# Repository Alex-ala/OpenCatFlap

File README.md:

OpenCatFlap
=====

Work in progress...

Being fed up with SurePets cat flap requiring cloud connection to properly work, I decided to design my own flap.
The 3D model is intended to fit into the SurePet adapter already installed.

I want my flap to have at least these features:
1. Easily managable via an API and/or WebUI/MQTT
2. Powered by battery OR power plug!
3. Easy install via AP/Wifi
4. Motion detection on both sides of the flap to check on where a cat is and where it moves to
5. Light barrier that detects into which direction the flap got opened
6. Light barrier in both sides of the "tunnel" to check into which direction the cat moved
7. Independent control of mechanic in and out control. (My cats outsmart SureFlap by letting each other out/in)
8. Two RFID sensors to detect cats on each side and possibly both!
9. Modular design to easily remove the cover, the electronics and the mechanical parts without having to unscrew screws from the outside.

In addition to that the software should be capable of everything SureFlap is capable of, plus:
1. Set pets as "outdoor only"
2. Quickly and more easily set specific per-cat permissions
3. Manually "unlock once" option for each direction

Current state:
------
**Hardware:**

It is bases on an ESP32 (Arduino Nano ESP32 for development) with various sensors and two servos to lock/unlock.
The 3D model is ready to be tested and a printed version is already in use to debug the code. Slight adjustments to the
antenna design will be done in future.

Used vital parts:
- 2x PIR (motion detection): Panasonic AMN33111, testing with cheaper options
- 2x light barrier for flap detection: TCST 1103
- 2x light barrier for tunnel passage: IR LED + NE555 and TSOP18*38 and TSOP18*56
- 2x RFID reader: EM4095
- 2x Servo: DSM44

**Software:**

The software runs a main process that handles global configs and aggregates events reported by the two state machines.
After the last hardware overhaul, quite some work is to be done to update sensors and reading RFID from EM4095 instead of WL-134

## State machines
The locking and unlocking logic is split up into two independent state machines, one for each direction of travel.
One state machine handles the PIR, RFID and Servo on one side of the cat flap.

This way the flap can idependently unlock for ougoing or incoing cats without acidentally opening the other direction aswell, allowing false passages.

Roughly speaking there are 3 states: Idle (only PIR active to wait for motion), Reading (RFID enabled when motion is detected) and unlocked (when a correct RFID is read).

## Wifi

If no Wifi is configured, the flap acts as an AP opening an open "OpenCatFlap" wifi. One can either use this wifi for full control via api, or send credentials to connect to an existing wifi.

## MQTT

MQTT can be configured to connect to an existing MQTT server. The flap will then send events to topics `opencatflap/<flapname>/<type>`.
Configuration via MQTT is planned.

## Webserver

Current means to configure the flap is via http. There is a webserver running on :80 that takes requests to configure wifi, mqtt, lock allowance and cats, aswell as getting some status information.

How to configure (for now):
Wifi: `curl -H "Content-Type: application/json" http://192.168.4.1/api -d '{"command": "wifiConfig", "ssid": "Bockenburg", "passphrase": "", "ntpServer": "ip preffered, hostname possible"}'`
MQTT: `curl -H "Content-Type: application/json" 'http://10.5.0.60/api' -d'{"command": "mqttConfig", "server": "mosquitto.ahome", "port": 8011, "ssl": true, "logActivity": true}'`
MQTT Certificates: 
```
curl -H "Content-Type: text/plain" 'http://10.5.0.60/api/certs?name=key' --data-binary @/home/alex/trash/opencatflap.key
curl -H "Content-Type: text/plain" 'http://10.5.0.60/api/certs?name=cert' --data-binary @/home/alex/trash/opencatflap.crt
curl -H "Content-Type: text/plain" 'http://10.5.0.60/api/certs?name=ca' --data-binary @/home/alex/trash/ca.crt
```

## Getting started with a new Arduino Nano ESP32

A new board ships with Arduino's stock partition table, which has no `spiffs` partition. DFU uploads only replace the app, so the first flash has to be done with esptool. Otherwise the webserver fails with `File system is not mounted`.

1. In `platformio.ini`, make sure `upload_protocol = esptool` is active in `[env:arduino_nano_esp32]`.
2. Optional: put `wifi_configuration.json`, `mqtt_configuration.json` and the MQTT certificates into `data/` to have them preinstalled. They are ignored by git and can also be set later via the API.
3. Close any serial monitor and enter bootloader mode: connect B1 to GND, press reset, then remove the connection. The board now shows up as `303a:1001` in `lsusb`.
4. Flash the bootloader, partition table and firmware:
   ```
   pio run -e arduino_nano_esp32 -t upload
   ```
5. Flash the filesystem. If the board left bootloader mode, repeat step 3 first. This replaces everything on the filesystem with the contents of `data/`.
   ```
   pio run -e arduino_nano_esp32 -t uploadfs
   ```
6. Press reset and wait about 20 seconds for the flap to boot.
7. Without a Wifi config, connect to the open "OpenCatFlap" wifi and open http://192.168.4.1. Configure Wifi and MQTT as described above.

The partition table only has to be flashed once per board. Afterwards, firmware updates can use DFU (comment out `upload_protocol = esptool`) or the `arduino_nano_esp32_ota` environment. Filesystem uploads always need esptool.

**Future Improvements:**
- NE555 is too inconsistant due to 5% tolerance capacitor with bad temperature coefficient
- Tuning condensators for EM4095 have to be bigger to allow more jiggle-room when building an antenna
- Condensators to configure EM4095 need to have better tolerance and temperature coefficient to get as close to required frequency as possible. Current ones allow reading big chips, small tubes and implanted ones need a lot of hugging the antenna.
- Cheaper connectors for the PCB and external sensors
- Battery backup circuit
- ESP32 directly onboard

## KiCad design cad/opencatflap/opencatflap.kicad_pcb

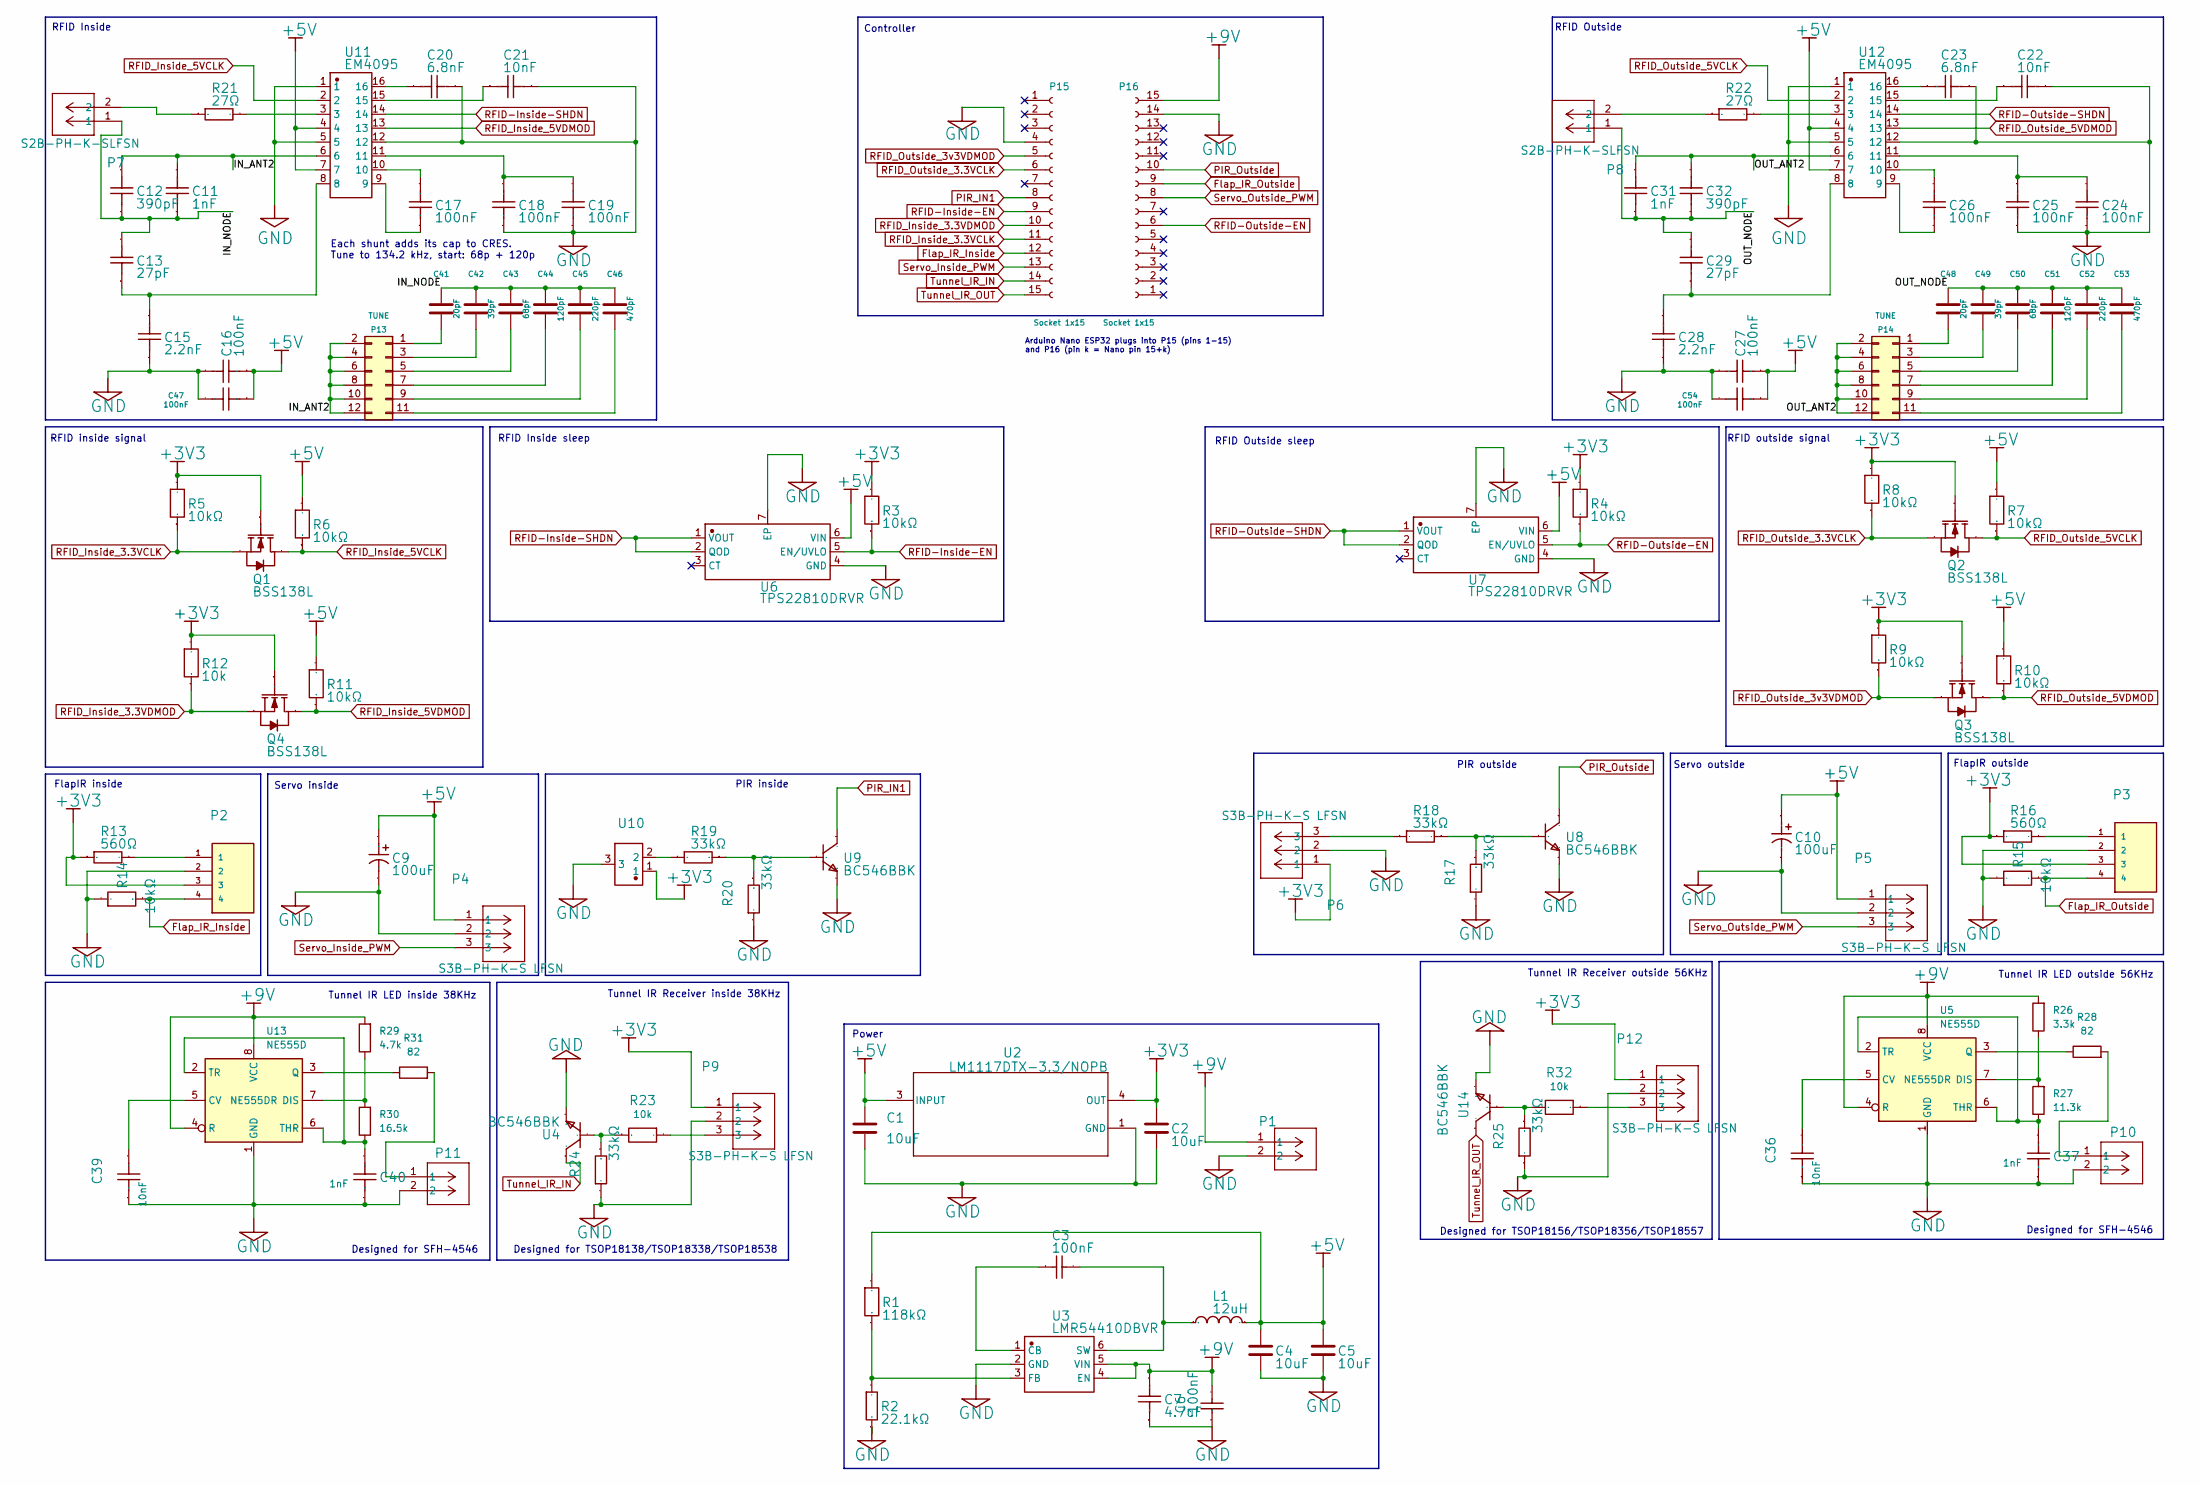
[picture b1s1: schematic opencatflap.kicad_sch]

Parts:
C1, C2, C4, C5: 10uF; CAP_CL31A_SAM; Manufacturer Part CL31A106KBHNNNE; LCSC C13585
C3, C6: 100nF; C_1210_3225Metric; Manufacturer Part CC1210KKX7R0BB104; LCSC C527375
C7: 4.7uF; C_1206_3216Metric; Manufacturer Part CC1206KKX7R9BB475; LCSC C132170
C9, C10: 100uF; CP_Elec_6.3x7.7; Manufacturer Part VH1E101ME077000CE0; LCSC C240513
C11, C31: 1nF; C_1206_3216Metric; Manufacturer Part CC1206JKNPOCBN102; LCSC C113872
C12, C32: 390pF; C_1206_3216Metric; Manufacturer Part CC1206JKNPOCBN391; LCSC C326659
C13, C29: 27pF; C_1206_3216Metric; Manufacturer Part CC1206JKNPOCBN270; LCSC C541492
C15, C28: 2.2nF; C_0603_1608Metric; Manufacturer Part CC0603FRNPO9BN222; LCSC C576780
C16, C17, C18, C19, C24, C25, C26, C27, C47, C54: 100nF; C_0603_1608Metric; Manufacturer Part CC0603KRX7R9BB104; LCSC C14663
C20, C23: 6.8nF; C_0603_1608Metric; Manufacturer Part 0603B682K500NT; LCSC C1631
C21, C22, C36, C39: 10nF; C_0603_1608Metric; Manufacturer Part 0603B103K500NT; LCSC C57112
C37, C40: 1nF; C_0603_1608Metric; Manufacturer Part CC0603FRNPO9BN102; LCSC C309468
C41, C48: 20pF; C_1206_3216Metric; Manufacturer Part CC1206JKNPOCBN200; LCSC C577124
C42, C49: 39pF; C_1206_3216Metric; Manufacturer Part CC1206JKNPOCBN390; LCSC C541493
C43, C50: 68pF; C_1206_3216Metric; Manufacturer Part CC1206JKNPOCBN680; LCSC C107178
C44, C51: 120pF; C_1206_3216Metric; Manufacturer Part CC1206JKNPOCBN121; LCSC C113873
C45, C52: 220pF; C_1206_3216Metric; Manufacturer Part CC1206JKNPOCBN221; LCSC C107175
C46, C53: 470pF; C_1206_3216Metric; Manufacturer Part CC1206JKNPOCBN471; LCSC C107177
L1: 12uH; L_Changjiang_FNR6045S; Manufacturer Part FNR6045S120MT; LCSC C168077
P1, P7, P8, P11: S2B-PH-K-SLFSN; CONN_S2B-PH-K-S_JST; Manufacturer Part S2B-PH-K-S(LF)(SN); LCSC C173752
P2, P3: S4B-PH-K-S_LF__SN_; CONN_S4B-PH-K-S_JST; Manufacturer Part S4B-PH-K-S(LF)(SN); LCSC C157926
P4, P5, P6, P9, P12: S3B-PH-K-S LFSN; CONN_S3B-PH-K-S_JST; Manufacturer Part S3B-PH-K-S(LF)(SN); LCSC C157929
P10: IL-G-2P-S3T2-SA; CONN_S2B-PH-K-S_JST; Manufacturer Part S2B-PH-K-S(LF)(SN); LCSC C173752
P13, P14: TUNE; PinHeader_2x06_P2.54mm_Vertical; Manufacturer Part HX PZ2.54-2x6P ZZ; LCSC C32713279
P15, P16: Socket 1x15; PinSocket_1x15_P2.54mm_Vertical; Manufacturer Part HX PM2.54-1x15P ZC; LCSC C41417327
Q1, Q2, Q3, Q4: BSS138L; Manufacturer Part BSS138L; LCSC C890265
R1: 118kΩ; R_0603_1608Metric; Manufacturer Part RT0603FRE07118KL; LCSC C863548
R2: 22.1kΩ; R_0603_1608Metric; Manufacturer Part RC0603FR-0722K1L; LCSC C137768
R3, R4, R5, R6, R7, R8, R9, R10, R11, R14, R15: 10kΩ; R_0603_1608Metric; Manufacturer Part 0603WAF1002T5E; LCSC C25804
R12, R23, R32: 10k; R_0603_1608Metric; Manufacturer Part 0603WAF1002T5E; LCSC C25804
R13, R16: 560Ω; R_0603_1608Metric; Manufacturer Part 0603WAF5600T5E; LCSC C23204
R17, R18, R19, R20, R24, R25: 33kΩ; R_0603_1608Metric; Manufacturer Part 0603WAF3302T5E; LCSC C4216
R21, R22: 27Ω; R_2512_6332Metric; Manufacturer Part RC2512FK-0727RL; LCSC C877905
R26: 3.3k; R_0603_1608Metric; Manufacturer Part 0603WAF3301T5E; LCSC C22978
R27: 11.3k; R_0603_1608Metric; Manufacturer Part 0603WAF1132T5E; LCSC C22860
R28, R31: 82; R_0603_1608Metric; Manufacturer Part RC0603FR-0782RL; LCSC C137676
R29: 4.7k; R_0603_1608Metric; Manufacturer Part 0603WAF4701T5E; LCSC C23162
R30: 16.5k; R_0603_1608Metric; Manufacturer Part 0603WAF1652T5E; LCSC C22812
U2: LM1117DTX-3.3/NOPB; LM1117DTX-3.3NOPB; Manufacturer Part LM1117DTX-3.3/NOPB; LCSC C73181
U3: LMR54410DBVR; U_SOT-23_TEX; Manufacturer Part LMR54410DBVR; LCSC C3200265
U4, U8, U9, U14: BC546BBK; TO-92L_Inline; Manufacturer Part BC546BBK; LCSC C3201532
U5, U13: NE555D; SOIC-8_3.9x4.9mm_P1.27mm; Manufacturer Part NE555DR; LCSC C7593
U6, U7: TPS22810DRVR; DRV0006A_NV; Manufacturer Part TPS22810DRVR; LCSC C527679
U10: SB312; PinHeader_1x03_P2.54mm_Vertical; Manufacturer Part SB312; LCSC C96133
U11, U12: EM4095; Manufacturer Part EM4095HMSO16B+; LCSC C17203964

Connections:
+3V3: C2.1, P2.3, P3.3, P6.1, P9.1, P12.1, Q1.1 (G), Q2.1 (G), Q3.1 (G), Q4.1 (G), R3.2, R4.2, R5.2, R8.2, R9.2, R12.2, R13.1, R16.1, U2.4 (OUT), U10.1
+5V: C1.1, C4.1, C5.1, C9.1, C10.1, C16.1, C27.1, C47.1, C54.1, L1.2, P4.1, P5.1, R1.2, R6.2, R7.2, R10.2, R11.2, U2.3 (INPUT), U6.6 (VIN), U7.6 (VIN), U11.4, U11.7, U12.4, U12.7
+9V: C6.2, C7.2, P1.1, P16.15, R26.2, R29.2, U3.4 (EN), U3.5 (VIN), U5.4 (R), U5.8 (VCC), U13.4 (R), U13.8 (VCC)
/IN_ANT2: C11.2, C12.2, P13.2, P13.4, P13.6, P13.8, P13.10, P13.12, U11.6
/IN_NODE: C11.1, C12.1, C13.2, C41.1, C42.1, C43.1, C44.1, C45.1, C46.1, P7.1
/OUT_ANT2: C31.2, C32.2, P14.2, P14.4, P14.6, P14.8, P14.10, P14.12, U12.6
/OUT_NODE: C29.2, C31.1, C32.1, C48.1, C49.1, C50.1, C51.1, C52.1, C53.1, P8.1
Flap_IR_Inside: P2.4, P15.12, R14.1
Flap_IR_Outside: P3.4, P16.9, R15.1
GND: C1.2, C2.2, C4.2, C5.2, C6.1, C7.1, C9.2, C10.2, C15.1, C16.2, C18.1, C19.1, C20.2, C21.2, C22.2, C23.2, C24.1, C25.1, C27.2, C28.1, C36.1, C37.1, C39.1, C40.1, C47.2, C54.2, P1.2, P2.2, P3.2, P4.2, P5.2, P6.2, P9.2, P10.2, P11.2, P12.2, P15.4, P16.14, R2.1, R14.2, R15.2, R17.2, R20.2, R24.2, R25.2, U2.1 (GND), U3.2 (GND), U4.3 (E), U5.1 (GND), U6.4 (GND), U6.7 (EP), U7.4 (GND), U7.7 (EP), U8.3 (E), U9.3 (E), U10.3, U11.1, U11.5, U11.12, U12.1, U12.5, U12.12, U13.1 (GND), U14.3 (E); also elsewhere on the board
unnamed: C13.1, C15.2, U11.8
unnamed: C17.1, U11.9
unnamed: C17.2, U11.10
unnamed: C18.2, C19.2, U11.11
unnamed: C20.1, U11.16
unnamed: C21.1, U11.15
unnamed: C22.1, U12.15
unnamed: C23.1, U12.16
unnamed: C24.2, C25.2, U12.11
unnamed: C26.1, U12.9
unnamed: C26.2, U12.10
unnamed: C28.2, C29.1, U12.8
unnamed: P2.1, R13.2
unnamed: P3.1, R16.2
unnamed: P6.3, R18.2
unnamed: P7.2, R21.1
unnamed: P8.2, R22.1
unnamed: P9.3, R23.2
unnamed: P10.1, R28.2
unnamed: P11.1, R31.2
unnamed: P12.3, R32.2
unnamed: C41.2, P13.1
unnamed: C42.2, P13.3
unnamed: C43.2, P13.5
unnamed: C44.2, P13.7
unnamed: C45.2, P13.9
unnamed: C46.2, P13.11
unnamed: C48.2, P14.1
unnamed: C49.2, P14.3
unnamed: C50.2, P14.5
unnamed: C51.2, P14.7
unnamed: C52.2, P14.9
unnamed: C53.2, P14.11
unnamed: R19.2, U10.2
unnamed: R21.2, U11.3
unnamed: R22.2, U12.3
unnamed: C3.1, U3.1 (CB)
unnamed: R1.1, R2.2, U3.3 (FB)
unnamed: C3.2, L1.1, U3.6 (SW)
unnamed: R23.1, R24.1, U4.2 (B)
unnamed: C36.2, U5.5 (CV)
unnamed: R26.1, R27.2, U5.7 (DIS)
unnamed: R28.1, U5.3 (Q)
unnamed: C37.2, R27.1, U5.2 (TR), U5.6 (THR)
unnamed: R17.1, R18.1, U8.2 (B)
unnamed: R19.1, R20.1, U9.2 (B)
unnamed: C39.2, U13.5 (CV)
unnamed: R29.1, R30.2, U13.7 (DIS)
unnamed: R31.1, U13.3 (Q)
unnamed: C40.2, R30.1, U13.2 (TR), U13.6 (THR)
unnamed: R25.1, R32.1, U14.2 (B)
PIR_IN1: P15.8, U9.1 (C)
PIR_Outside: P16.10, U8.1 (C)
RFID-Inside-EN: P15.9, R3.1, U6.5 (EN/UVLO)
RFID-Inside-SHDN: U6.1 (VOUT), U6.2 (QOD), U11.14
RFID-Outside-EN: P16.6, R4.1, U7.5 (EN/UVLO)
RFID-Outside-SHDN: U7.1 (VOUT), U7.2 (QOD), U12.14
RFID_Inside_3.3VCLK: P15.11, Q1.2 (S), R5.1
RFID_Inside_3.3VDMOD: P15.10, Q4.2 (S), R12.1
RFID_Inside_5VCLK: Q1.3 (D), R6.1, U11.2
RFID_Inside_5VDMOD: Q4.3 (D), R11.1, U11.13
RFID_Outside_3.3VCLK: P15.6, Q2.2 (S), R8.1
RFID_Outside_3v3VDMOD: P15.5, Q3.2 (S), R9.1
RFID_Outside_5VCLK: Q2.3 (D), R7.1, U12.2
RFID_Outside_5VDMOD: Q3.3 (D), R10.1, U12.13
Servo_Inside_PWM: P4.3, P15.13
Servo_Outside_PWM: P5.3, P16.8
Tunnel_IR_IN: P15.14, U4.1 (C)
Tunnel_IR_OUT: P15.15, U14.1 (C)

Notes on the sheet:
FlapIR inside
Tunnel IR Receiver outside 56KHz
FlapIR outside
Designed for TSOP18138/TSOP18338/TSOP18538
Controller
PIR outside
Tunnel IR LED inside 38KHz
Servo outside
Designed for SFH-4546
Arduino Nano ESP32 plugs into P15 (pins 1-15) and P16 (pin k = Nano pin 15+k)
Designed for TSOP18156/TSOP18356/TSOP18557
RFID Outside
RFID inside signal
RFID Outside sleep
Power
Servo inside
RFID outside signal
PIR inside
RFID Inside
RFID Inside sleep
Tunnel IR LED outside 56KHz
Tunnel IR Receiver inside 38KHz
Each shunt adds its cap to CRES. Tune to 134.2 kHz, start: 68p + 120p

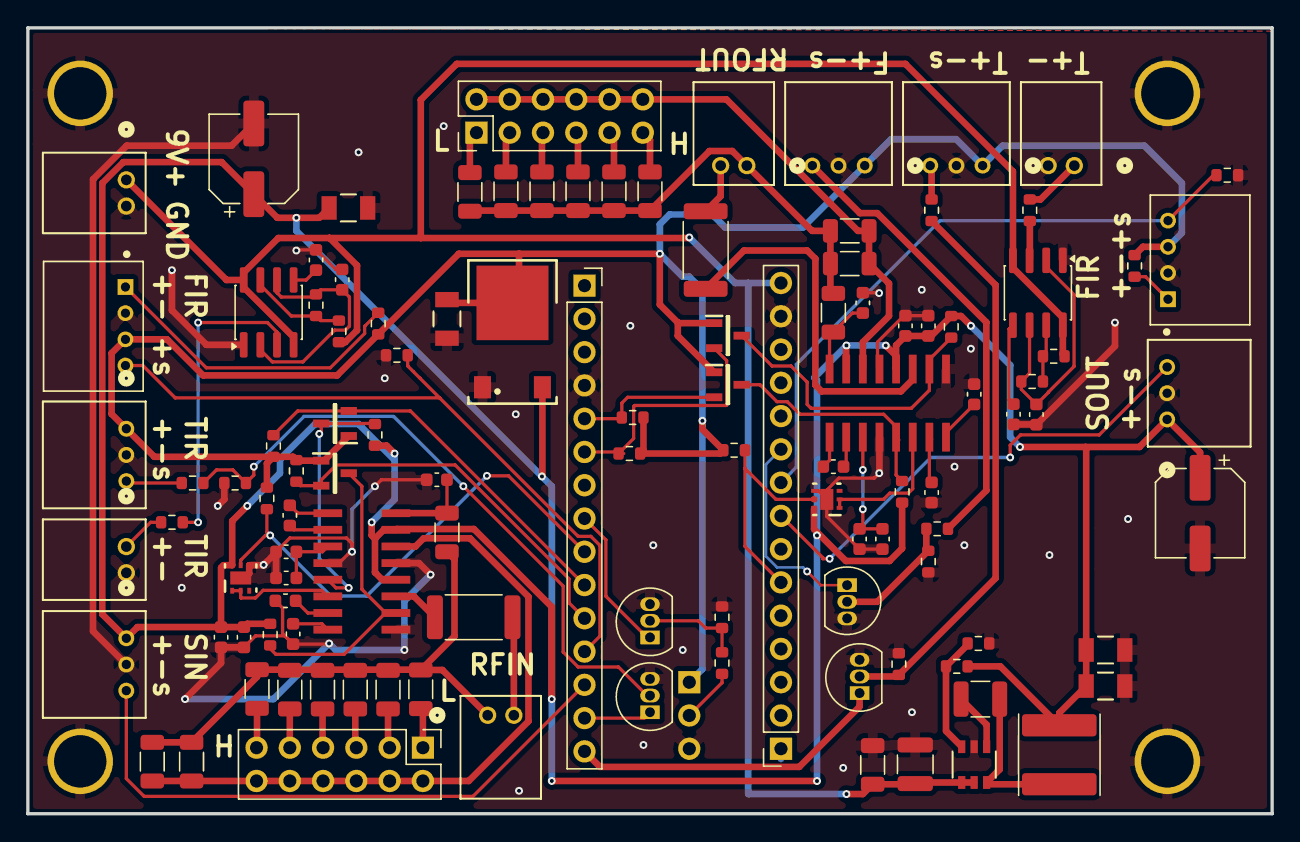
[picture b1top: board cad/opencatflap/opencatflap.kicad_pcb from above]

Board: 2 copper layers, 95.0 x 60.0 mm, 117 parts (1 on the bottom side), 79 nets.

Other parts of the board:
Pad_gge19202, Pad_gge19226, Pad_gge19274, Pad_gge19274#2: Bohrloch

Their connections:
GND: Pad_gge19202.1, Pad_gge19226.1, Pad_gge19274.1, Pad_gge19274#2.1; also elsewhere on the board

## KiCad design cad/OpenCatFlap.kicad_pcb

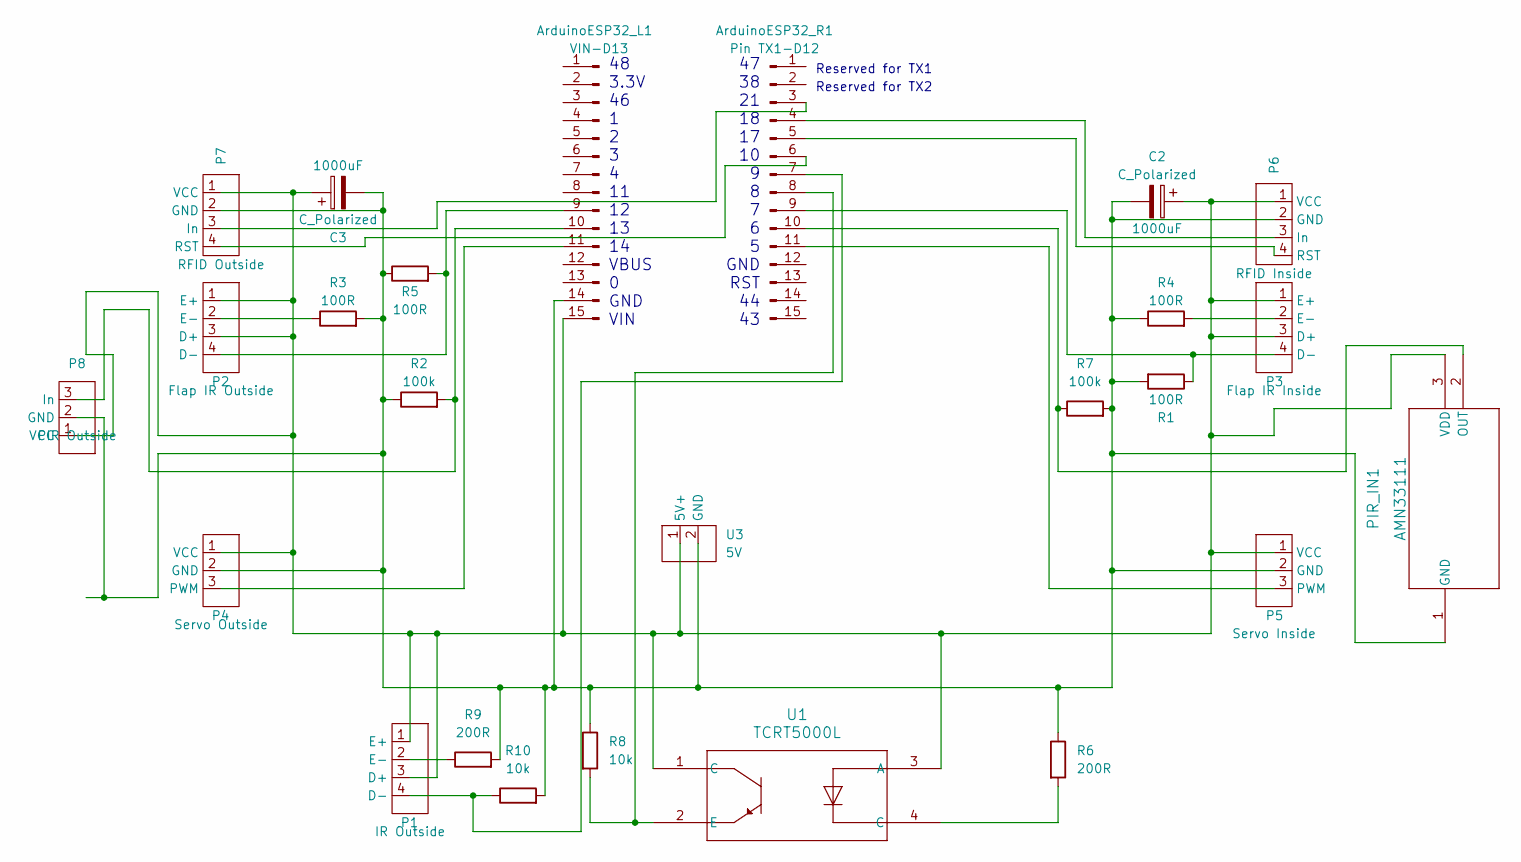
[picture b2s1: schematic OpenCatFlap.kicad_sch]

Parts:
ArduinoESP32_L1: VIN-D13; PinHeader_1x15_P2.54mm_Vertical
ArduinoESP32_R1: Pin TX1-D12; PinHeader_1x15_P2.54mm_Vertical
C2, C3: C_Polarized; CP_Elec_8x10
P1: IR Outside; PinHeader_1x04_P2.54mm_Vertical
P2: Flap IR Outside; PinHeader_1x04_P2.54mm_Vertical
P3: Flap IR Inside; PinHeader_1x04_P2.54mm_Vertical
P4: Servo Outside; PinHeader_1x03_P2.54mm_Vertical
P5: Servo Inside; PinHeader_1x03_P2.54mm_Vertical
P6: RFID Inside; PinHeader_1x04_P2.54mm_Vertical
P7: RFID Outside; PinHeader_1x04_P2.54mm_Vertical
P8: PIR Outside; PinHeader_1x03_P2.54mm_Vertical
PIR_IN1: AMN33111; AMN33111_PAN
R1, R3, R4, R5: 100R; R_0805_2012Metric
R2, R7: 100k; R_0805_2012Metric
R6, R9: 200R; R_0805_2012Metric
R8, R10: 10k; R_0805_2012Metric
U1: TCRT5000L; TCRT5000_VIS
U3: 5V; PinHeader_1x02_P2.54mm_Vertical

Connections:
unnamed: ArduinoESP32_L1.9, P2.4 (D-), R5.2
unnamed: ArduinoESP32_L1.10, P8.3 (In), R2.2
unnamed: ArduinoESP32_L1.11, P4.3 (PWM)
unnamed: ArduinoESP32_L1.14, C2.2, C3.2, P4.2 (GND), P5.2 (GND), P6.2 (GND), P7.2 (GND), P8.2 (GND), PIR_IN1.1 (GND), R1.2, R2.1, R3.2, R4.1, R5.1, R6.1, R7.2, R8.1, R9.2, R10.2, U3.2 (GND)
unnamed: ArduinoESP32_L1.15, C2.1, C3.1, P1.1 (E+), P1.3 (D+), P2.1 (E+), P2.3 (D+), P3.1 (E+), P3.3 (D+), P4.1 (VCC), P5.1 (VCC), P6.1 (VCC), P7.1 (VCC), P8.1 (VCC), PIR_IN1.3 (VDD), U1.1 (C), U1.3 (A), U3.1 (5V+)
unnamed: ArduinoESP32_R1.3, P7.3 (In)
unnamed: ArduinoESP32_R1.4, P6.3 (In)
unnamed: ArduinoESP32_R1.5, P6.4 (RST)
unnamed: ArduinoESP32_R1.6, P7.4 (RST)
unnamed: ArduinoESP32_R1.7, P1.4 (D-), R10.1
unnamed: ArduinoESP32_R1.8, R8.2, U1.2 (E)
unnamed: ArduinoESP32_R1.9, P3.4 (D-), R1.1
unnamed: ArduinoESP32_R1.10, PIR_IN1.2 (OUT), R7.1
unnamed: ArduinoESP32_R1.11, P5.3 (PWM)
unnamed: P1.2 (E-), R9.1
unnamed: P2.2 (E-), R3.1
unnamed: P3.2 (E-), R4.2
unnamed: R6.2, U1.4 (C)

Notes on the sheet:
Reserved for TX2
48 3.3V 46 1 2 3 4 11 12 13 14 VBUS 0 GND VIN
47 38 21 18 17 10 9 8 7 6 5 GND RST 44 43
Reserved for TX1

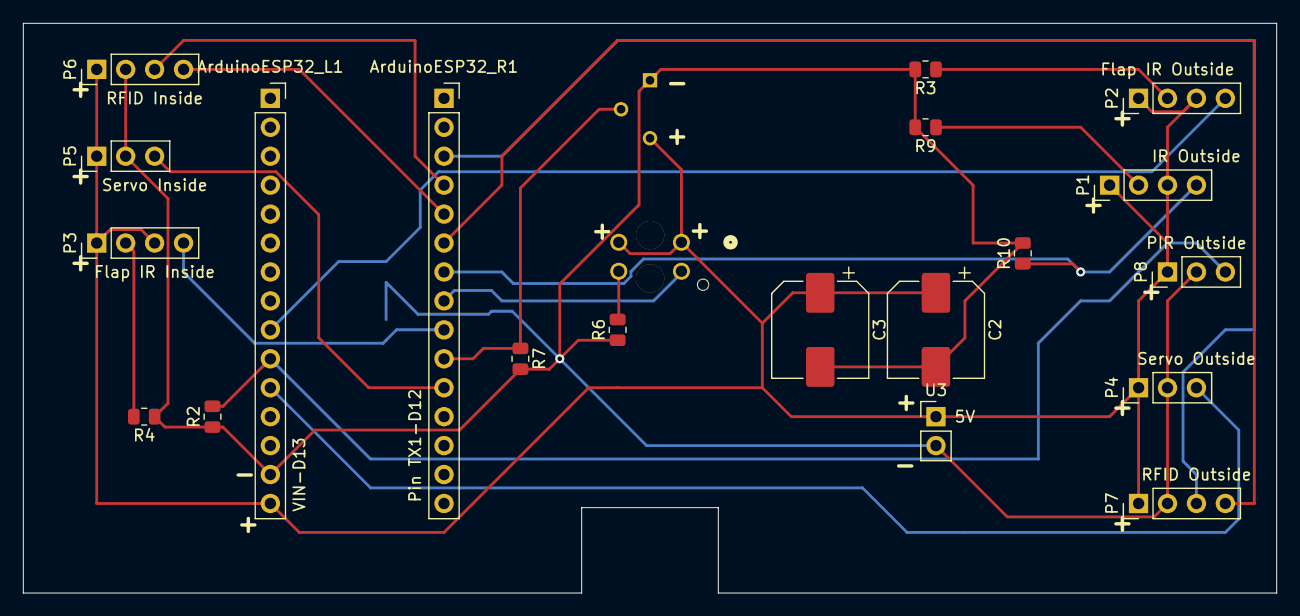
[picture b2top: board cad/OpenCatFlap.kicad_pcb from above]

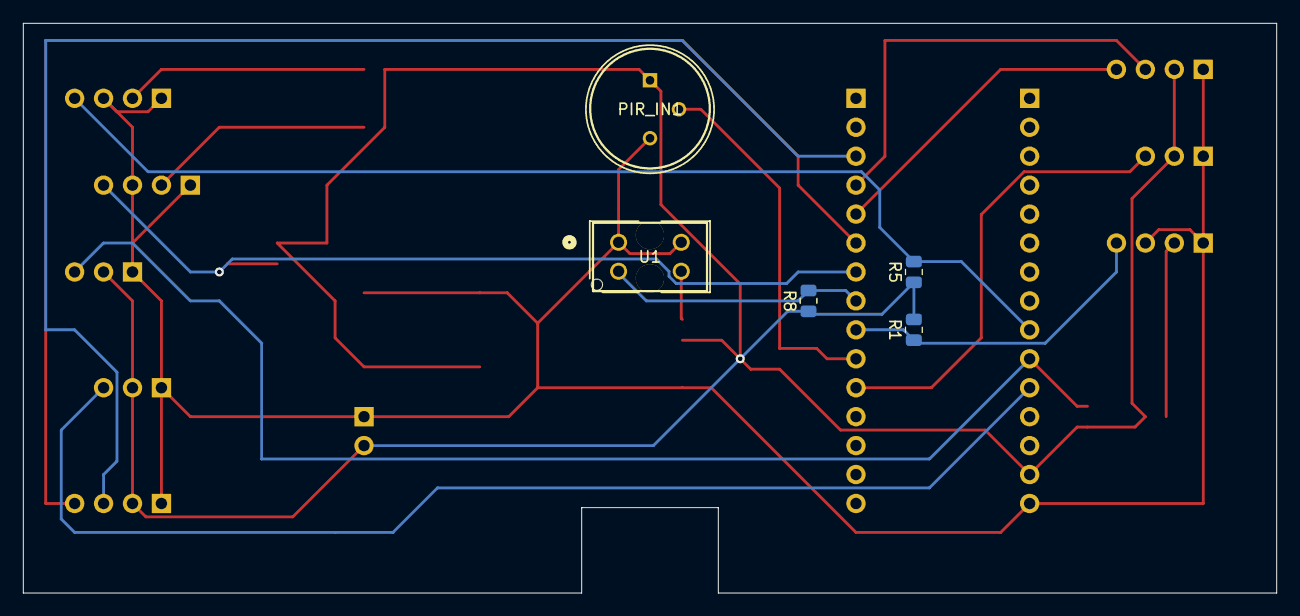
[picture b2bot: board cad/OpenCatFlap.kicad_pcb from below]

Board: 2 copper layers, 110.0 x 50.0 mm, 25 parts (5 on the bottom side), 18 nets.

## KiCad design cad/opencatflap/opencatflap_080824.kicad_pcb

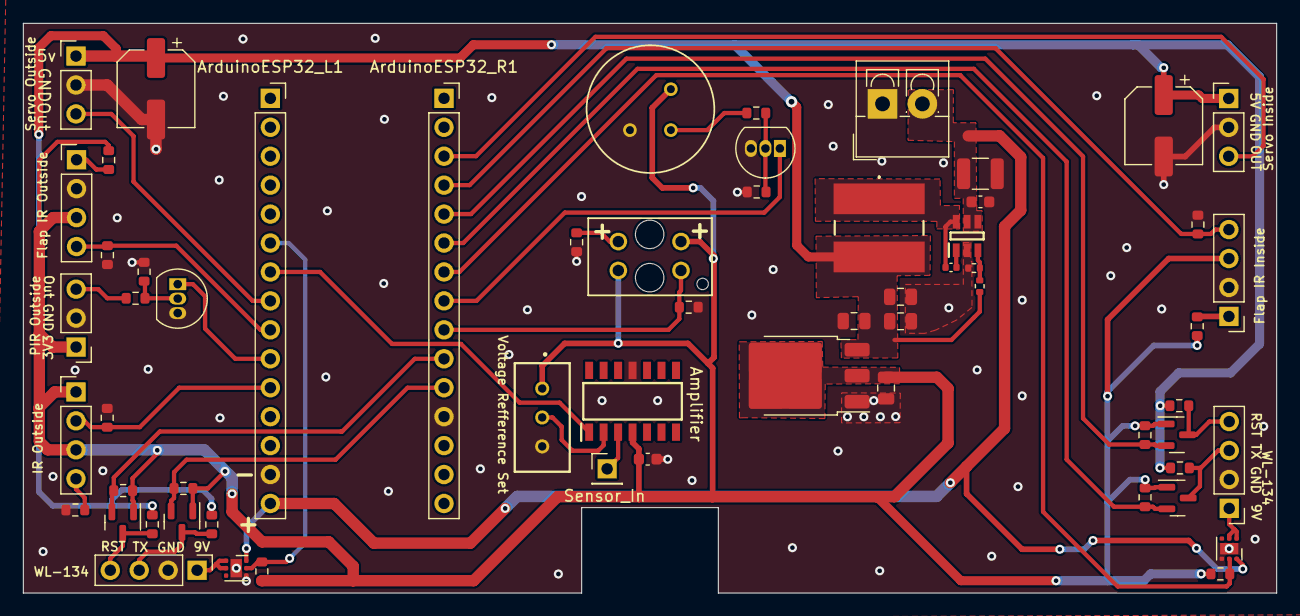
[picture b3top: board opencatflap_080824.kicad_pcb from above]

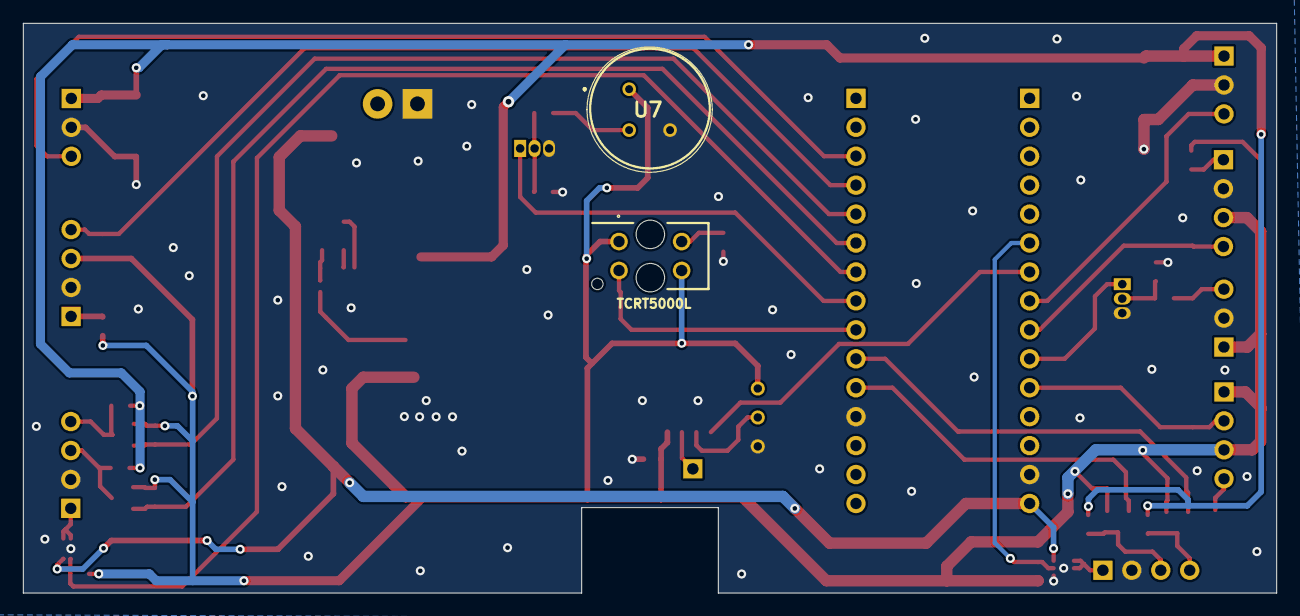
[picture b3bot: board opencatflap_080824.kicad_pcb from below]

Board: 2 copper layers, 110.0 x 50.0 mm, 61 parts (2 on the bottom side), 38 nets.

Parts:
ArduinoESP32_L1: VIN-D13; PinSocket_1x15_P2.54mm_Vertical
ArduinoESP32_R1: Pin TX1-D12; PinSocket_1x15_P2.54mm_Vertical
C1, C2, C5, C7: 10u; C_0805_2012Metric
C3: 100n; C_0402_1005Metric
C4: 4.7u; C_1210_3225Metric
C6, C10: 100n; C_0603_1608Metric
C8, C9: 100u; CP_Elec_6.3x7.7
J1: Screw_Terminal_01x02; TerminalBlock_4Ucon_1x02_P3.50mm_Vertical
J2: Screw_Terminal_01x04; PinHeader_1x04_P2.54mm_Vertical
J3: Screw_Terminal_01x01; PinHeader_1x01_P2.54mm_Vertical
L1: 12u; SDR0805120ML
P1: PIR Outside; PinHeader_1x03_P2.54mm_Vertical
P2: Flap IR Inside; PinHeader_1x04_P2.54mm_Vertical
P4: Flap IR Outside; PinHeader_1x04_P2.54mm_Vertical
P9: RFID Inside; PinHeader_1x04_P2.54mm_Vertical
P10: RFID OutSide; PinHeader_1x04_P2.54mm_Vertical
P11: Servo Inside; PinHeader_1x03_P2.54mm_Vertical
P12: Servo Outside; PinHeader_1x03_P2.54mm_Vertical
Q1, Q2, Q3, Q4: BSS138; SOT-23
Q5, Q6: BC546B; TO-92_Inline
R1, R26: 200R; R_0603_1608Metric
R2, R7, R8, R9: 33k; R_0603_1608Metric
R3, R4, R6, R11, R12, R13, R14, R15, R16, R18, R20, R22, R24, R25: 10k; R_0603_1608Metric
R5, R21: 566R; R_0603_1608Metric
R10: 118k; R_0402_1005Metric
R23: 22.1k; R_0402_1005Metric
RV1: 10k; 3296W-1
U1, U2: TPS22810DRV; WSON-6-1EP_2x2mm_P0.65mm_EP1x1.6mm
U3: LM1117DT-3.3; TO-252-3_TabPin2
U4: LM324; SOIC127P600X175-14N
U5: TCRT5000L
U6: LMR54410DBVR
U7: AMN33111

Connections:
+3V3: C2.1, C10.1, J2.1, J2.3, P1.1 (VCC), P2.3 (D+), P4.3 (D+), Q1.1 (G), Q2.1 (G), Q3.1 (G), Q4.1 (G), R4.1, R5.2, R11.1, R13.1, R15.1, R16.1, R20.1, R21.2, RV1.1, U3.2 (VO), U4.4 (V+), U5.1 (C), U5.3 (A), U7.1 (VDD)
+5V: C1.1, C5.1, C7.1, C8.1, C9.1, L1.2, P11.1 (VCC), P12.1 (VCC), R6.1, R10.1, R12.1, R14.1, R18.1, U3.3 (VI)
+9V: ArduinoESP32_L1.15, C4.1, C6.1, J1.2, U1.6 (VIN), U2.6 (VIN), U6.4 (EN), U6.5 (VIN)
/CB: C3.2, U6.1 (CB)
/FB: R10.2, R23.1, U6.3 (FB)
/PIR_Out: R2.1, U7.2 (OUT)
/SW: C3.1, L1.1, U6.6 (SW)
Amplifier_Out: ArduinoESP32_L1.7, U4.1
Flap_IR_Inside: ArduinoESP32_R1.4, P2.4 (D-), R24.1
Flap_IR_Outside: ArduinoESP32_L1.9, P4.4 (D-), R22.1
GND: ArduinoESP32_L1.14, ArduinoESP32_R1.12, C1.2, C2.2, C4.2, C5.2, C6.2, C7.2, C8.2, C9.2, C10.2, J1.1, P1.2 (GND), P2.2 (E-), P4.2 (E-), P9.2 (GND), P10.2 (GND), P11.2 (GND), P12.2 (GND), Q5.3 (E), Q6.3 (E), R1.2, R3.2, R7.2, R9.2, R22.2, R23.2, R24.2, R25.2, R26.2, RV1.3, U1.4 (GND), U1.7 (GND), U2.4 (GND), U2.7 (GND), U3.1 (GND), U4.11 (V-), U6.2 (GND), U7.3 (GND)
IR_Outside: ArduinoESP32_L1.11, J2.2, R25.1
unnamed: J2.4, R26.1
unnamed: J3.1, U4.3 (+)
unnamed: P1.3 (In), R8.1
unnamed: P2.1 (E+), R5.1
unnamed: P4.1 (E+), R21.1
unnamed: Q5.2 (B), R8.2, R9.1
unnamed: Q6.2 (B), R2.2, R7.1
unnamed: R1.1, U5.4 (C)
unnamed: RV1.2, U4.2 (-)
PIR_IN1: ArduinoESP32_R1.8, Q6.1 (C)
PIR_Outside: ArduinoESP32_L1.10, Q5.1 (C)
RFID-Inside-EN: ArduinoESP32_R1.7, R15.2, U2.5 (EN/UVLO)
RFID-Outside-EN: ArduinoESP32_L1.6, R20.2, U1.5 (EN/UVLO)
RFID_Inside_3.3VRST: ArduinoESP32_R1.5, Q2.2 (S), R13.2
RFID_Inside_3v3VIN: ArduinoESP32_R1.6, Q1.2 (S), R11.2
RFID_Inside_5VIN: P9.3 (In), Q1.3 (D), R12.2
RFID_Inside_5VRST: P9.4 (RST), Q2.3 (D), R14.2
RFID_Inside_Vin: P9.1 (VCC), U2.1 (VOUT), U2.2 (QOD)
RFID_Outside_3.3VRST: ArduinoESP32_R1.10, Q4.2 (S), R4.2
RFID_Outside_3v3VIN: ArduinoESP32_R1.11, Q3.2 (S), R16.2
RFID_Outside_5VIN: P10.3 (In), Q3.3 (D), R18.2
RFID_Outside_5VRST: P10.4 (RST), Q4.3 (D), R6.2
RFID_Outside_Vin: P10.1 (VCC), U1.1 (VOUT), U1.2 (QOD)
Servo_Inside_PWM: ArduinoESP32_R1.3, P11.3 (PWM)
Servo_Outside_PWM: ArduinoESP32_L1.8, P12.3 (PWM)
TCRT5000L: ArduinoESP32_R1.9, R3.1, U5.2 (E)

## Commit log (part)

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2023-06-03 Init
2023-06-03 removed asynchttpserver dependency
2023-06-03 add more definitions to start with hardware implementation
2023-06-03 Test lock control via debug endpoint. Automatically lock after 2s
2023-06-04 debug motion sensors
2023-06-10 line feeds. And motion control
2023-06-10 persist state
2023-06-11 hurz
2023-06-16 Prepare for evaluation run
2023-06-16 more robust opening/closing
2023-06-17 Test direction detection
2023-06-17 Better value for inside servo
2023-06-17 Use NTP
2023-07-08 woop woop works without intereferences now
2023-07-08 add bad schematics
2023-07-15 meowqtt
2023-09-10 add cad
2023-09-10 meowqtt works
2023-09-10 more mqtt
2023-09-18 make everything ugly, but OOP LUL
2023-09-19 improvements
2023-10-13 meow
2023-10-14 update readme with parts
2023-10-15 Revert "meow"
    This reverts commit 70150f40207d0a9de3da7c8185f4e8c8306b4b66.
2023-10-21 repo cleanup
2023-10-30 add rfid init
2024-01-02 boop
2024-01-03 Fix wiring
2024-03-28 board v2
2024-03-28 update schematics
2024-07-06 Run on new mainboard
2024-07-07 rfid test
2024-07-07 test rfid, update cad
2024-08-11 initial work
2024-08-11 blurgh
2024-09-22 statemachine
2024-10-05 Fix compile
2024-10-13 it compiles. No clue if it runs
2024-10-14 roughly working version
2024-12-01 fix rfid
2024-12-14 wörk
2024-12-14 cat control working
2024-12-14 remove old files
2024-12-15 mqtt, fix rfid logging, add html config
2024-12-21 add mqtt messages for rfid and locks
2025-07-20 init new rfid tests
2025-07-20 rfid works-ish (need checksum tests)
2025-10-05 cleanup
2025-12-13 works
2025-12-13 a little beautify
2025-12-13 rearrange
2025-12-16 Not functional yet, but first todos to go with new RFID code.
2025-12-21 test
2025-12-22 RFID works. no logic implemented yet
2026-01-18 init logic
